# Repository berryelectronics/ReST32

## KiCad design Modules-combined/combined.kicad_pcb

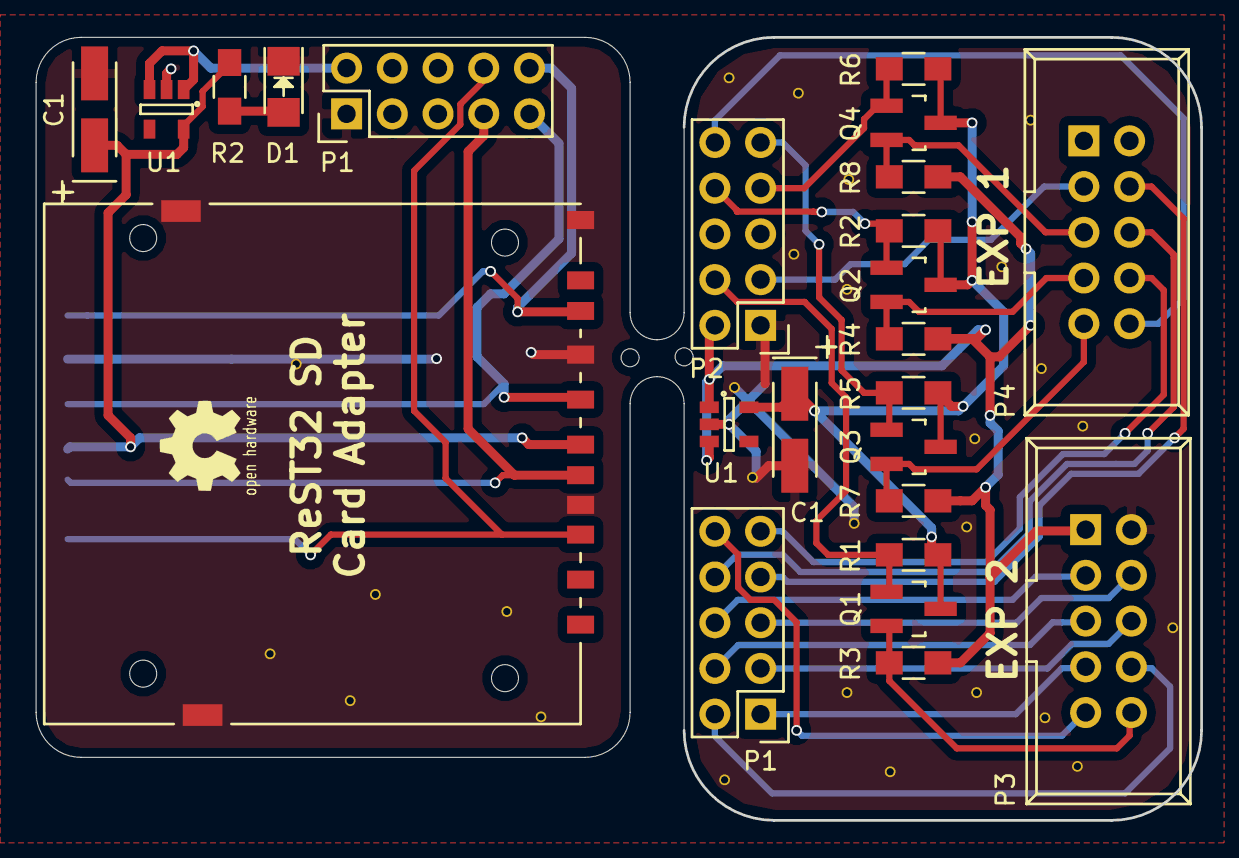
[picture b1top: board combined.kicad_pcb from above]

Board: 2 copper layers, 64.8 x 43.5 mm, 25 parts (1 on the bottom side), 28 nets.

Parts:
C1: 2.2uF; TantalC_SizeA_EIA-3216_HandSoldering
C1#2: CP1_Small; TantalC_SizeA_EIA-3216_HandSoldering
CON1, CON2: uSD_Card; SD_Card_Receptacle
D1: Led_Small; LED_1206
P1, P1#2, P2: CONN_02X05; Pin_Header_Straight_2x05
P3, P4: CONN_02X05; IDC_Header_Straight_10pins
Q1, Q2, Q3, Q4: BSS138; SOT-23_Handsoldering
R1, R2, R3, R4, R5, R6, R7, R8: 10K; R_0805_HandSoldering
R2#2: 1K; R_0805_HandSoldering
U1, U1#2: MIC5205; SOT-23-5

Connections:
+3V3: C1.1, C1#2.1, CON1.4, CON2.4, Q1.3, Q2.3, Q3.3, Q4.3, R1.1, R2.1, R2#2.1, R5.1, R6.1, U1.5, U1#2.5
+5V: P1#2.2, P2.2, P3.1, R3.1, R4.1, R7.1, R8.1, U1.1, U1.3, U1#2.1, U1#2.3
/BEEP: P3.10, Q1.2, R3.2
/CS: P4.7, Q2.2, R4.2
/DISPLAY_CD: P1.2, P3.8
/DISPLAY_CS: P1.1, P3.7
/DISPLAY_D0: P1.4, P3.5
/DISPLAY_D1: P1.3, P3.6
/DISPLAY_D2: P1.6, P3.3
/DISPLAY_D3: P1.5, P3.4
/DISPLAY_D4: P1.8, P4.6
/DISPLAY_D5: P1.7, P4.4
/DISPLAY_D6: P1.10, P3.9
/DISPLAY_D7: P1.9, P4.8
/DISPLAY_RD: P2.3, P4.3
/DISPLAY_WR: P2.4, Q1.1, R1.2
/MISO: P2.10, P4.10
/MOSI: P4.5, Q4.2, R8.2
/SCK: P4.9, Q3.2, R7.2
/SPI-CS: CON1.2, CON2.2, P1#2.8
/SPI-MISO: CON1.7, CON2.7, P1#2.10
/SPI-MOSI: CON1.3, CON2.3, P1#2.7
/SPI-SCK: CON1.5, CON2.5, P1#2.9
/SPI_CS1: P2.8, Q2.1, R2.2
/SPI_MOSI: P2.7, Q4.1, R6.2
/SPI_SCK: P2.9, Q3.1, R5.2
GND: C1.2, C1#2.2, CON1.6, CON1.10, CON1.11, CON1.12, CON1.13, CON2.6, CON2.10, CON2.11, CON2.12, CON2.13, D1.1, P1#2.1, P2.1, P3.2, U1.2, U1#2.2
unnamed: D1.2, R2#2.2

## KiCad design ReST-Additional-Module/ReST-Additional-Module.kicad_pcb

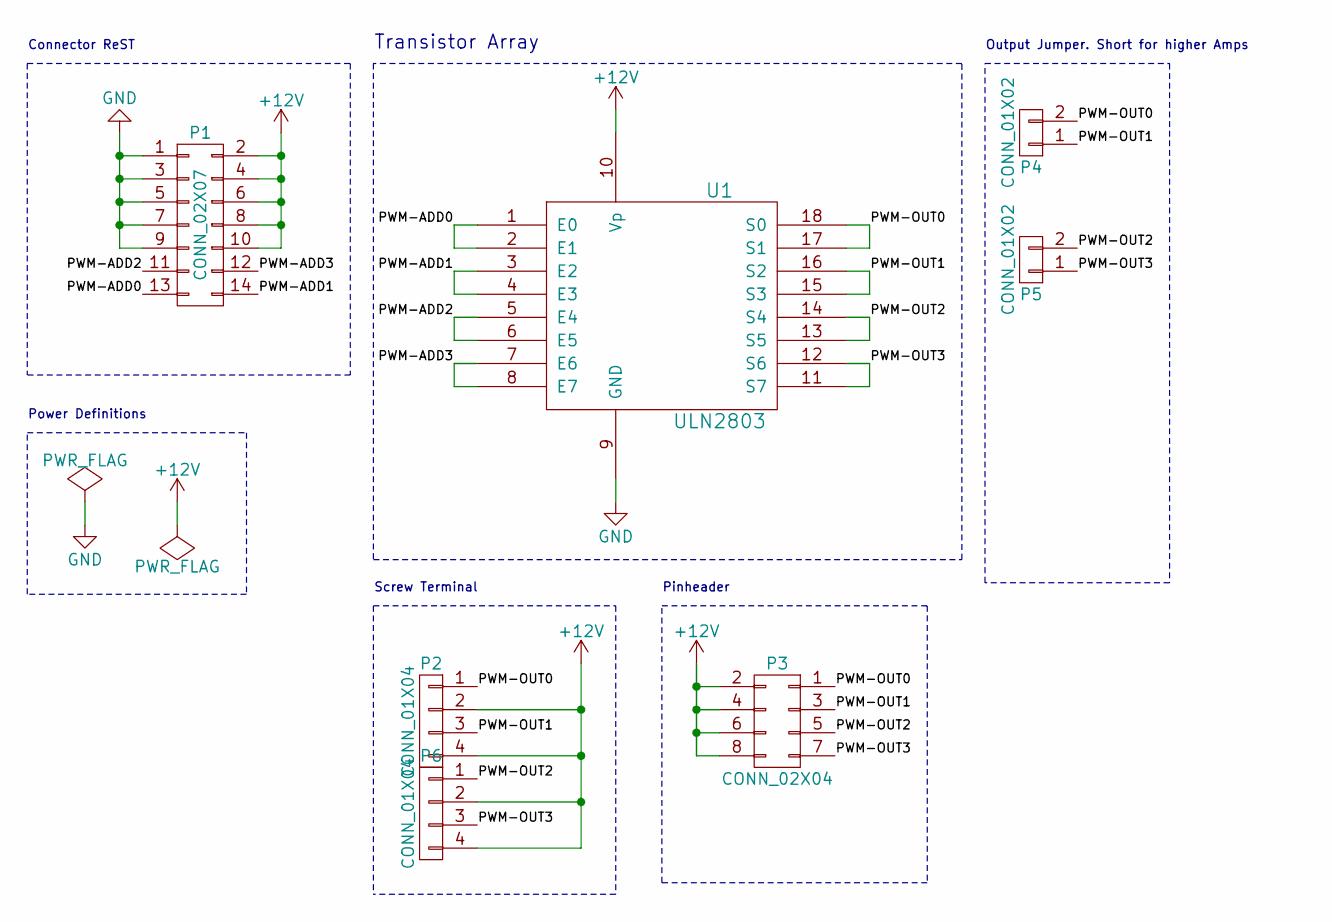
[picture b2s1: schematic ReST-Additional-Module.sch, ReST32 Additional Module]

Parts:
P1: CONN_02X07; Pin_Header_Angled_2x07
P2, P6: CONN_01X04; screw-2,54-4P
P3: CONN_02X04; Pin_Header_Straight_2x04
P4, P5: CONN_01X02; Pin_Header_Straight_1x02
U1: ULN2803; DIP-18_W7.62mm_LongPads

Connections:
+12V: P1.2, P1.4, P1.6, P1.8, P1.10, P2.2, P2.4, P3.2, P3.4, P3.6, P3.8, P6.2, P6.4, U1.10 (Vp)
/PWM-ADD0: P1.13, U1.1 (E0), U1.2 (E1)
/PWM-ADD1: P1.14, U1.3 (E2), U1.4 (E3)
/PWM-ADD2: P1.11, U1.5 (E4), U1.6 (E5)
/PWM-ADD3: P1.12, U1.7 (E6), U1.8 (E7)
/PWM-OUT0: P2.1, P3.1, P4.2, U1.17 (S1), U1.18 (S0)
/PWM-OUT1: P2.3, P3.3, P4.1, U1.15 (S3), U1.16 (S2)
/PWM-OUT2: P3.5, P5.2, P6.1, U1.13 (S5), U1.14 (S4)
/PWM-OUT3: P3.7, P5.1, P6.3, U1.11 (S7), U1.12 (S6)
GND: P1.1, P1.3, P1.5, P1.7, P1.9, U1.9 (GND)

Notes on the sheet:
Connector ReST
Power Definitions
Pinheader
Output Jumper. Short for higher Amps
Screw Terminal
Transistor Array

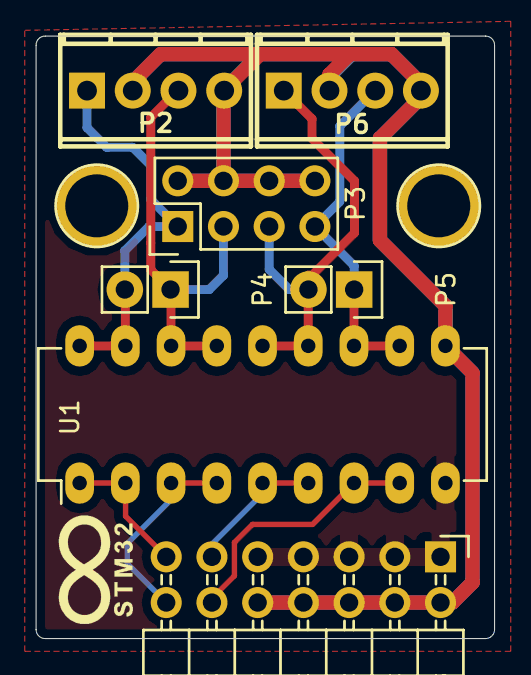
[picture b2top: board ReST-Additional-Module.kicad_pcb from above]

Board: 2 copper layers, 25.5 x 33.5 mm, 7 parts (0 on the bottom side), 10 nets.

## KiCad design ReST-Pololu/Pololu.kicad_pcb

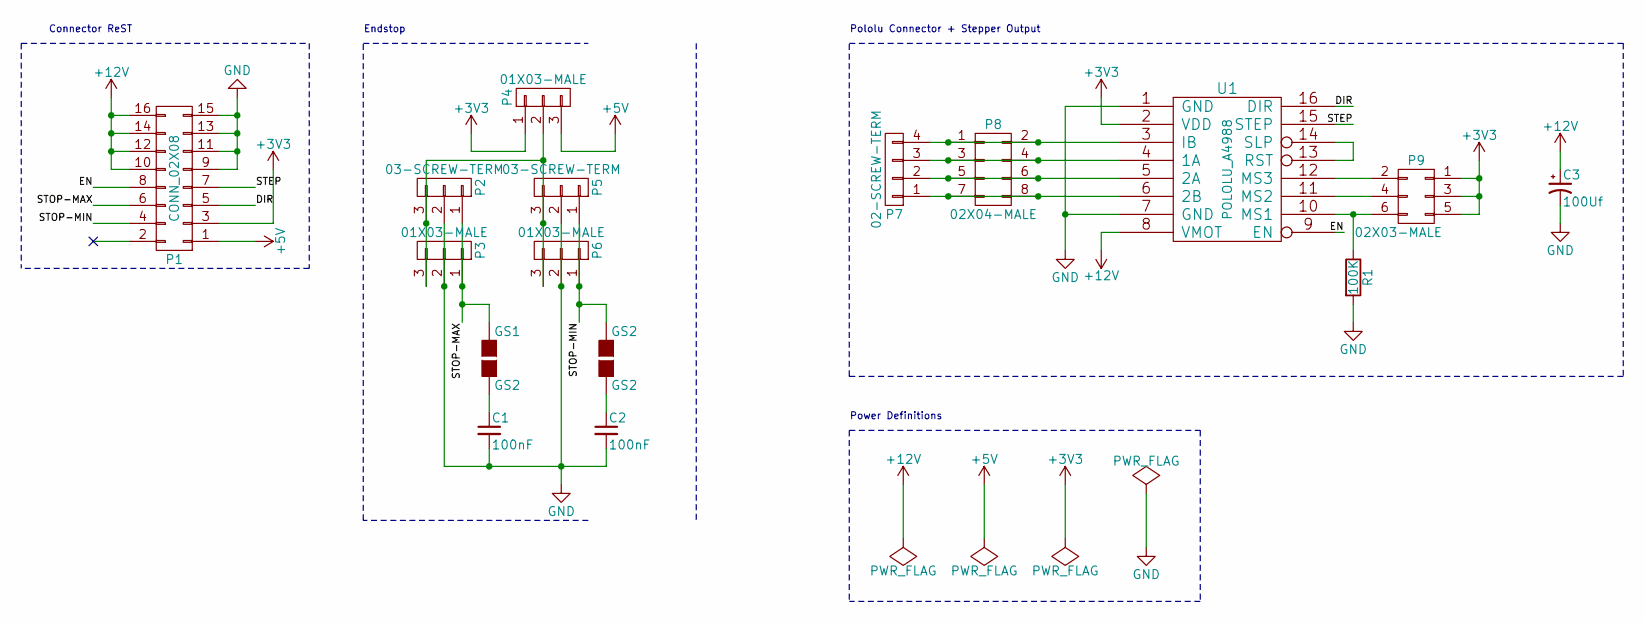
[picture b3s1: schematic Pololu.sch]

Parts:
C1, C2: 100nF; 1206
C3: 100Uf; c_elec_5x5.3
GS1, GS2: GS2
P1: CONN_02X08; Pin_Header_Angled_2x08
P2, P5: 03-SCREW-TERM; mpt_0,5%2f3-2,54
P3, P4, P6: 01X03-MALE; Pin_Header_Straight_1x03
P7: 02-SCREW-TERM; mpt_0,5%2f4-2,54
P8: 02X04-MALE; Pin_Header_Straight_2x04
P9: 02X03-MALE; Pin_Header_Straight_2x03
R1: 100K; 1206
U1: POLOLU_A4988; SWDIP8_.6W

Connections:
+3V3: P1.3, P4.1, P9.1, P9.3, P9.5, U1.2 (VDD)
+5V: P1.1, P4.3
+12V: C3.1, P1.10, P1.12, P1.14, P1.16, U1.8 (VMOT)
/DIR: P1.5, U1.16 (DIR)
/EN: P1.8, U1.9 (EN)
/STEP: P1.7, U1.15 (STEP)
/STOP-MAX: GS1.1 (G1), P1.6, P2.1, P3.1
/STOP-MIN: GS2.1 (G1), P1.4, P5.1, P6.1
GND: C1.2, C2.2, C3.2, P1.9, P1.11, P1.13, P1.15, P2.2, P3.2, P5.2, P6.2, R1.2, U1.1 (GND), U1.7 (GND)
unnamed: C1.1, GS1.2 (G2)
unnamed: C2.1, GS2.2 (G2)
unnamed: P2.3, P3.3, P4.2, P5.3, P6.3
unnamed: P7.1, P8.7, P8.8, U1.6 (2B)
unnamed: P7.2, P8.5, P8.6, U1.5 (2A)
unnamed: P7.3, P8.3, P8.4, U1.4 (1A)
unnamed: P7.4, P8.1, P8.2, U1.3 (IB)
unnamed: P9.2, U1.12 (MS3)
unnamed: P9.4, U1.11 (MS2)
unnamed: P9.6, R1.1, U1.10 (MS1)
unnamed: U1.13 (RST), U1.14 (SLP)

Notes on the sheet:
Connector ReST
Endstop
Pololu Connector + Stepper Output
Power Definitions

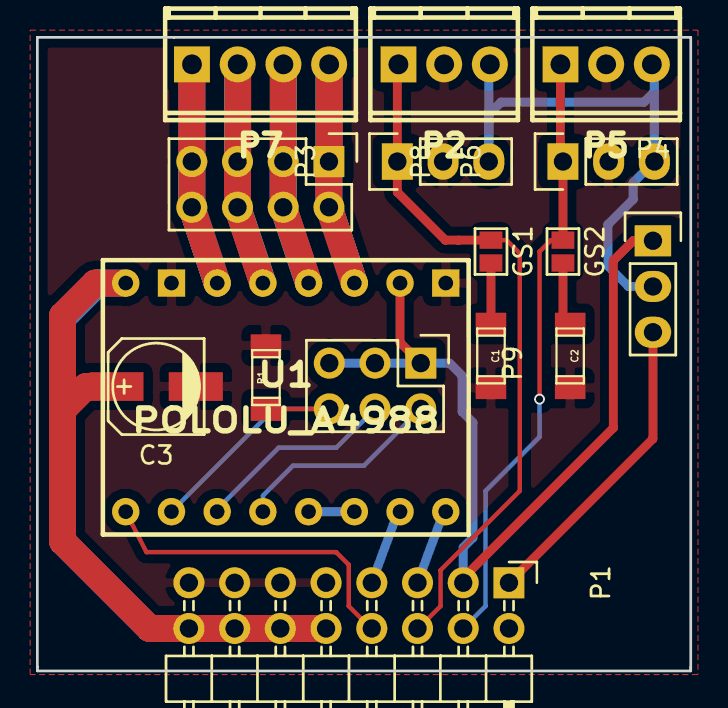
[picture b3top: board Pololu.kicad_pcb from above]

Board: 2 copper layers, 36.3 x 35.2 mm, 16 parts (0 on the bottom side), 20 nets.

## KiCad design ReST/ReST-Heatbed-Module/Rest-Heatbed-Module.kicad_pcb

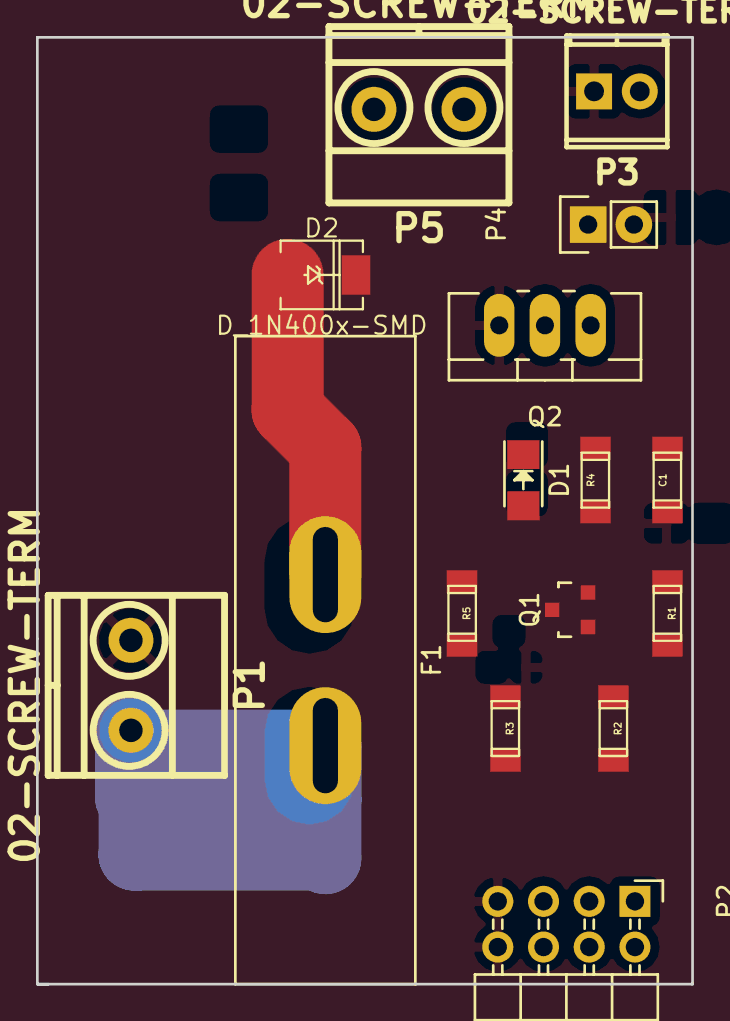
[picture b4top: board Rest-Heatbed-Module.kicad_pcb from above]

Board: 2 copper layers, 36.4 x 52.6 mm, 16 parts (0 on the bottom side), 11 nets.

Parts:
C1: 10uF; 1206
D1: LED; LED_1206
D2: D_1N400x-SMD; DO-214AC(SMA)
F1: 15A; JEF-703C
P1, P5: 02-SCREW-TERM; mkds_1,5-2
P2: 02X04-MALE; Pin_Header_Angled_2x04
P3: 02-SCREW-TERM; mpt_0,5%2f2-2,54
P4: 01X02-MALE; Pin_Header_Straight_1x02
Q1: Q_BSH105; SOT-23
Q2: Q_AOT240L; TO-220_Neutral123_Vertical_LargePads
R1: 4.7K; 1206
R2, R3: 100K; 1206
R4: 22R; 1206
R5: 470R; 1206

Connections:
+3V3: P2.2, P2.4, R1.2, R2.2
+5V: P2.1, P2.3, R3.2, R5.2
+12V: D2.1, F1.2, P5.2
/PWM-HEATBED: P2.6, Q1.1, R2.1
/T0: C1.1, P2.5, P3.2, P4.2, R1.1
GND: C1.2, P1.1, P2.7, P2.8, P3.1, P4.1, Q1.2, Q2.3
unnamed: D1.1, Q2.1, R4.2
unnamed: D1.2, R5.1
unnamed: D2.2, P5.1, Q2.2
unnamed: F1.1, P1.2
unnamed: Q1.3, R3.1, R4.1
